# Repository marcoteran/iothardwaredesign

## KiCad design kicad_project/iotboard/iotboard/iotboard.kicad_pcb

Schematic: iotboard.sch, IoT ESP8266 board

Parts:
C1, C3: 1u; C_0603_HandSoldering
C2, C4, C6, C8: 10u; C_0603_HandSoldering
C5: 4.7u; C_0603_HandSoldering
C7, C9: 100n; C_0603_HandSoldering
D1: D_Schottky; D_0603
D2, D3: LED; LED_0805_HandSoldering
J1: Conn_01x02; JST_XH_S02B-XH-A_02x2.50mm_Angled
J2: USB_B_Micro; USB_Micro-B_Molex_47346-0001
J3: Conn_01x12; Socket_Strip_Straight_1x12_Pitch2.54mm
J4: Conn_01x16; Socket_Strip_Straight_1x16_Pitch2.54mm
MH1, MH2, MH3, MH4: MountingHole_Pad; MountingHole_2.5mm_Pad_Via
Q1, Q2: mmbt2222; SOT-23
R1, R2, R3, R4, R8, R10, R11, R13, R14: 10k; R_0603_HandSoldering
R5: 2k; R_0603_HandSoldering
R6, R9, R12: 1k; R_0603_HandSoldering
R7: 4k7; R_0603_HandSoldering
SW1, SW2: SW_Push; SW_SPST_PTS645
U1: AP2127K-3.3; SOT-23-5_HandSoldering
U2: CP2102N-A01-GQFN24; QFN-24-1EP_4x4mm_Pitch0.5mm
U3: MCP73831-2-OT; SOT-23-5_HandSoldering
U4: DHT11; Aosong_DHT11_5.5x12.0_P2.54mm
U5: ESP-12F; ESP-12E

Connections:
+3V3: C3.1, C4.1, C7.1, C8.1, C9.1, D3.2, J4.15, R1.1, R7.2, R8.1, R10.1, R11.1, R14.1, U1.5 (VOUT), U4.1, U5.8 (VCC)
+BATT: C5.1, C6.1, D1.2, J1.1, J3.1, U3.3 (VBAT)
ADC0: J4.12, U5.2 (ADC)
DTR: Q1.3, R4.1, U2.23
EN: J4.1, R11.2, U5.3 (CH_PD)
EN_R: J3.2, R2.2, U1.3 (EN)
GND: C1.2, C2.2, C3.2, C4.2, C5.2, C6.2, C7.2, C8.2, C9.2, J1.2, J2.5, J4.13, MH1.1, MH2.1, MH3.1, MH4.1, R5.2, R13.2, SW1.1, SW2.1, U1.2 (GND), U2.2, U2.25, U3.2 (VSS), U4.4, U5.9 (GND)
GPIO0: J3.8, Q1.2, R12.2, U5.12 (GPIO0)
GPIO2: J3.10, R7.1, R14.2, U4.2, U5.11 (GPIO2)
GPIO4_SDA: J3.12, U5.13 (GPIO4)
GPIO5_SCL: J3.11, U5.14 (GPIO5)
GPIO12_MISO: J3.5, J4.4, U5.6 (GPIO12)
GPIO13_MOSI: J3.6, J4.5, U5.7 (GPIO13)
GPIO14_SCK: J3.4, J4.6, U5.5 (GPIO14)
GPIO15: J3.7, R8.2, R13.1, SW1.2, U5.10 (GPIO15)
GPIO16: J3.9, U5.4 (GPIO16)
unnamed: C1.1, U2.5, U2.6
unnamed: D2.1, R6.1
unnamed: D3.1, R12.1
unnamed: J2.2, U2.4
unnamed: J2.3, U2.3
unnamed: Q1.1, R3.2
unnamed: Q2.1, R4.2
unnamed: R1.2, U2.9
unnamed: R5.1, U3.5 (PROG)
unnamed: R9.1, U5.15 (RXD)
RST: J4.16, Q2.2, R10.2, SW2.2, U5.1 (REST)
RTS: Q2.3, R3.1, U2.19
RXD: J4.3, R9.2, U2.21
STAT: R6.2, U3.1 (STAT)
TXD: J4.2, U2.20, U5.16 (TXD)
VBUS: C2.1, D1.1, D2.2, J2.1, J3.3, R2.1, U1.1 (VIN), U2.7, U2.8, U3.4 (VDD)

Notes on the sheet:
ESP8266 Module
Reset
USB to serial converter
LED
Power
Charger
Temperature and humity sensor
Push button
Pinout

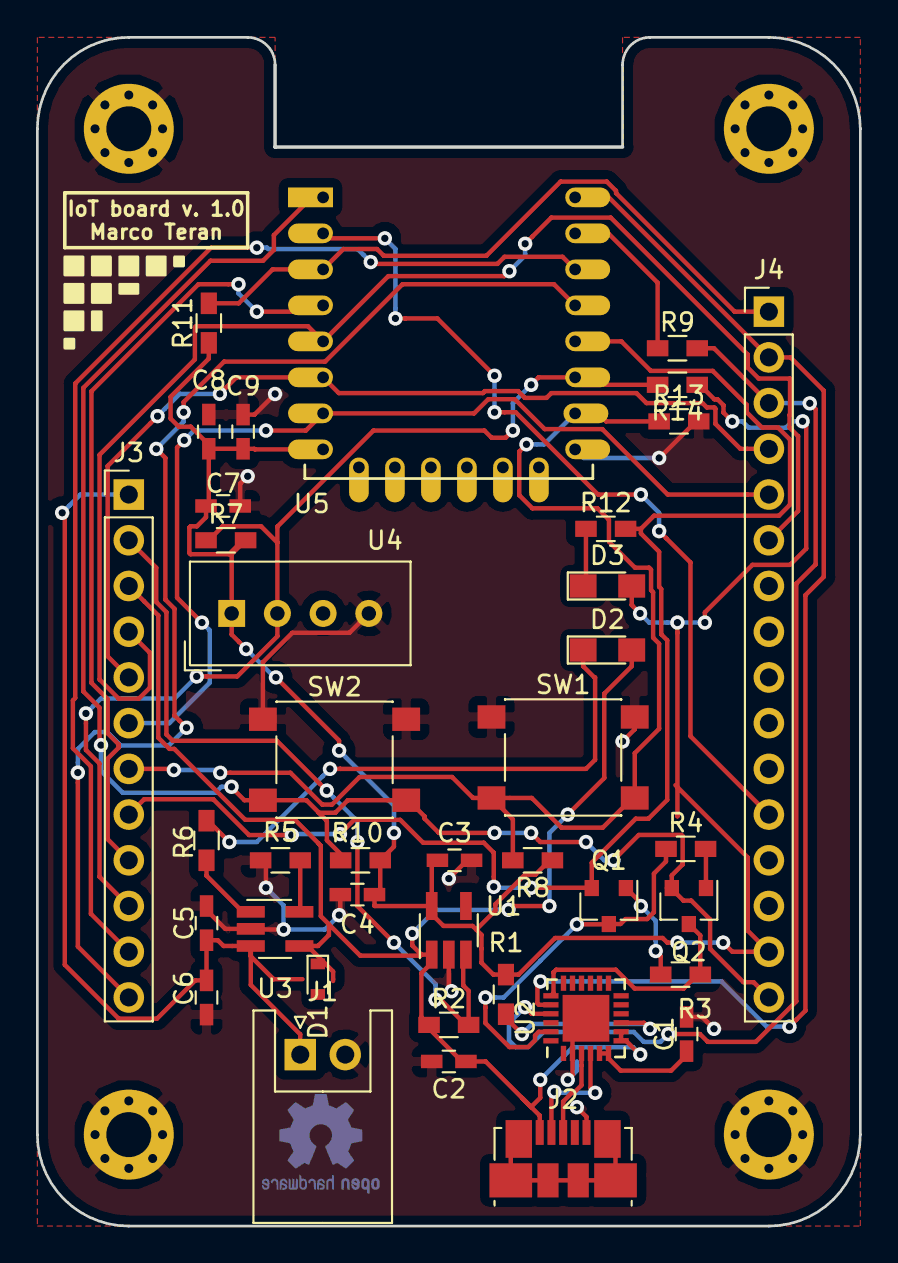
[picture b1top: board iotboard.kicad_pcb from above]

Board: 2 copper layers, 45.7 x 66.0 mm, 43 parts (0 on the bottom side), 32 nets.

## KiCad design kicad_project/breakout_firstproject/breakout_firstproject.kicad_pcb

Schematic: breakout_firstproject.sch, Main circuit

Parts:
D1: LED; LED_0603_HandSoldering
J1, J2: Conn_01x04_Male; Pin_Header_Straight_1x04_Pitch2.54mm
R1: 1k; R_0603_HandSoldering
U1: nrf24l01; nrf24l01_custom

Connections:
+3V3: D1.2, U1.2; also elsewhere on the board
CE: J1.2, U1.3
CSN: J2.2, U1.4
GND: J1.1, R1.2, U1.1; also elsewhere on the board
IRQ: J2.4, U1.8
MISO: J1.4, U1.7
MOSI: J2.3, U1.6
unnamed: D1.1, R1.1
SCK: J1.3, U1.5
VCC: J2.1; also elsewhere on the board

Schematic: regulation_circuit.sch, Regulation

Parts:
C1, C3: 10u; CP_Elec_6.3x5.3
C2, C4: 104; C_0603_HandSoldering
U2: LM1117-3.3; SOT-223

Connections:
+3V3: C3.1, C4.1, U2.2 (VO); also elsewhere on the board
GND: C1.2, C2.2, C3.2, C4.2, U2.1 (GND); also elsewhere on the board
VCC: C1.1, C2.1, U2.3 (VI); also elsewhere on the board

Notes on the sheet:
Voltaje de alimentación: 5 V

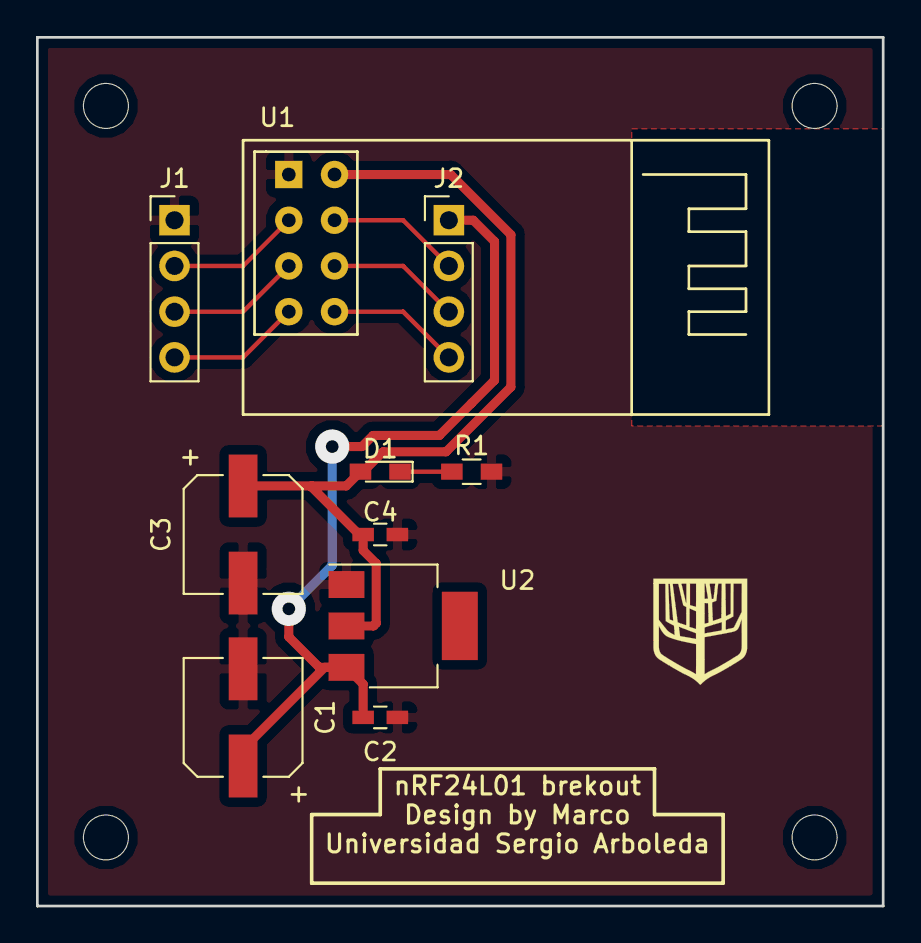
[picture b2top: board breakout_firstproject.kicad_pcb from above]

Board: 2 copper layers, 47.0 x 48.3 mm, 10 parts (0 on the bottom side), 10 nets.

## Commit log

2020-08-18 updating the README
2020-09-08 updated material and slides
2020-09-17 added the project example
2020-09-17 added some modiffications
2020-09-19 added Git cheat sheet
2020-10-15 added PCB design slides
2020-10-22 added the kicad project
2020-10-27 added some rules
2020-10-27 added PCB final and gebers
2020-10-27 Added BOM example
2020-11-10 added iot board slide
2020-11-10 added datasheet
2020-11-10 added datasheets and project
2020-11-12 added the PCB layout, some libraries
2020-11-20 added KiCAD PCB y project
